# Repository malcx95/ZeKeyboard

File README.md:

# ZeKeyboard

ZeKeyboard is a series of home-made RGB-backlit mechanical keyboards, 
with 3D-printed bodies and custom firmware. 3 keyboards have been made,
one with 60% layout, one with a full size layout, and most recently one
with a 60% layout plus a numpad (the "V2" keyboard). This repository contains all the source
code for the firmware, as well as the 3D-models of the keyboards.

## Layout and body

The first keyboard was the one with the 60% layout, pictured below. It uses the ANSI-style Enter-key,
as well as the ISO-style left-shift key.

The layout for this keyboard was partially generated using scripts and 
template OpenSCAD-files by [TheZoq2](https://github.com/TheZoq2/), which
you can find [here](https://github.com/TheZoq2/Keyboard). These OpenSCAD-files
contained the switch holes corresponding to the json-layout generated from 
[here](http://www.keyboard-layout-editor.com/), and were modeled further
in Blender to form a keyboard body.

The layout for the fullsize keyboard (picture unavailable) and the V2 keyboard (pictured below)
could not be generated using the aforementioned script, so they were manually modeled
in Blender from the json-layout generated from [here](http://www.keyboard-layout-editor.com/).
The V2 body also features carbon fibre handrests.

## Switches

All keyboards use Gateron Brown mechanical switches, which are very similar to 
Cherry MX Brown, in the sense that they have tactile feedback without a click. These
particular switches are the SMD-LED-compatible ones, meaning they have a white body
with clear top, and a large hole for an SMD-LED to shine through.

## Backlight

The backlight consists of Adafruit Neopixel RGB-LEDs. Each LED is hot-glued in place
right below each switch to shine through the 
hole in the switch, lighting up the keycap. This lights
each keycap up more uniformly than LED:s mounted right below the keycap.
On the 60% and V2 keyboard are also two extra LED:s for the spacebar, to the left and right of the main LED.

On the V2 keyboard, there are three LED:s shining inside a cavity in the handrest, illuminating
the ZeKeyboard logo.

## Controller

For the 60% keyboard, the controller used is a Teensy 3.2. I could have chosen a cheaper Teensy, like
Teensy LC, but I wanted enough computing power for the effects I was going to implement.
Also, at the time of purchase, I had a different approach to implementing the 
backlight (involving five TLC5940 chips), which required the extra ports available on the
more expensive Teensy 3.2.

For the other keyboards, due to the larger number of keys, a Teensy 3.5 is used, as it's faster
and has more RAM.

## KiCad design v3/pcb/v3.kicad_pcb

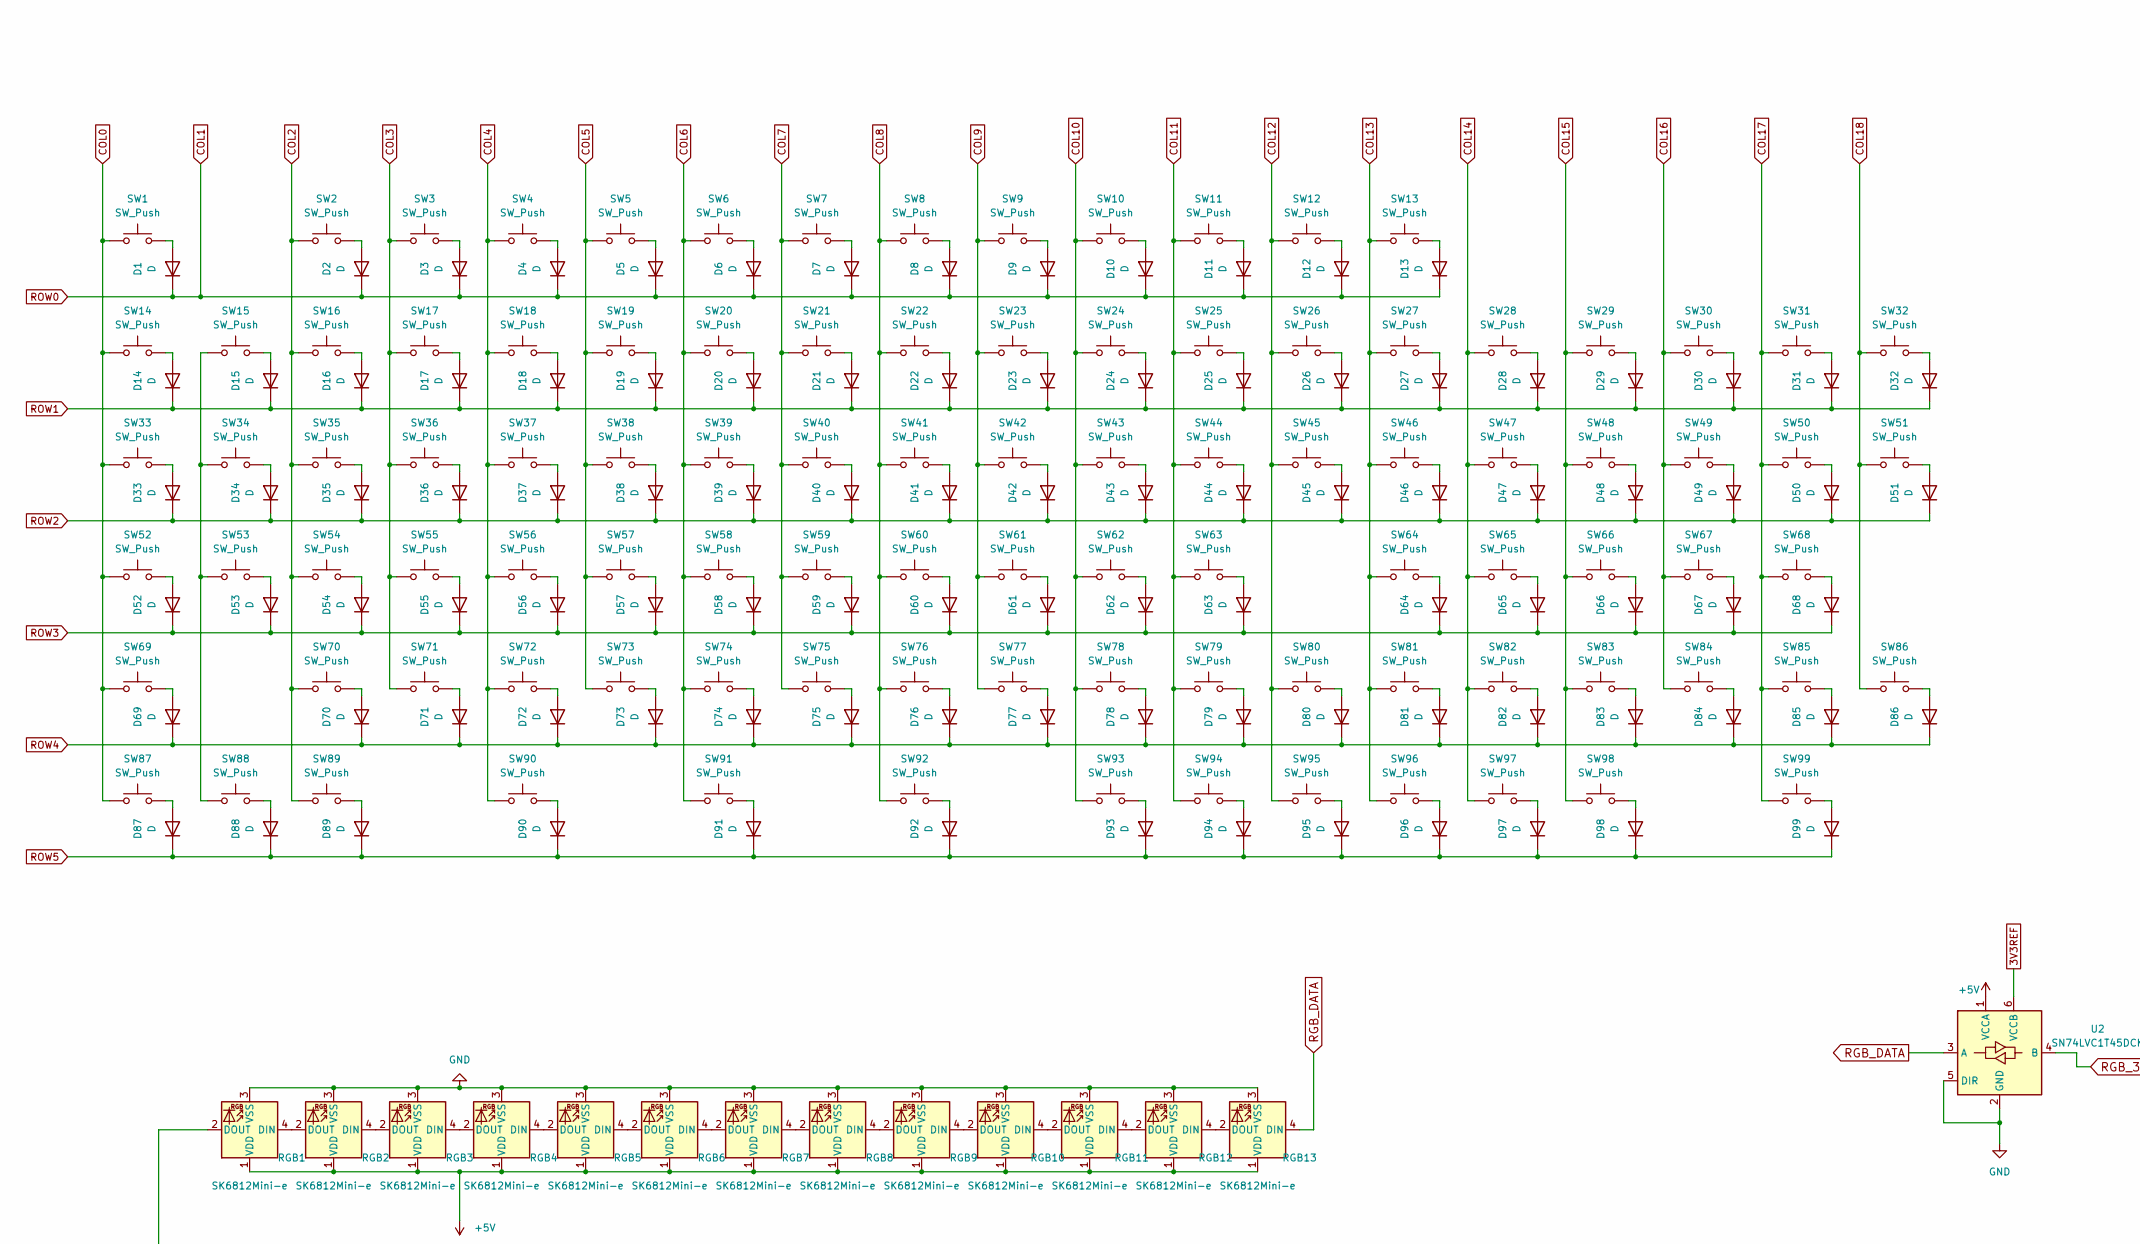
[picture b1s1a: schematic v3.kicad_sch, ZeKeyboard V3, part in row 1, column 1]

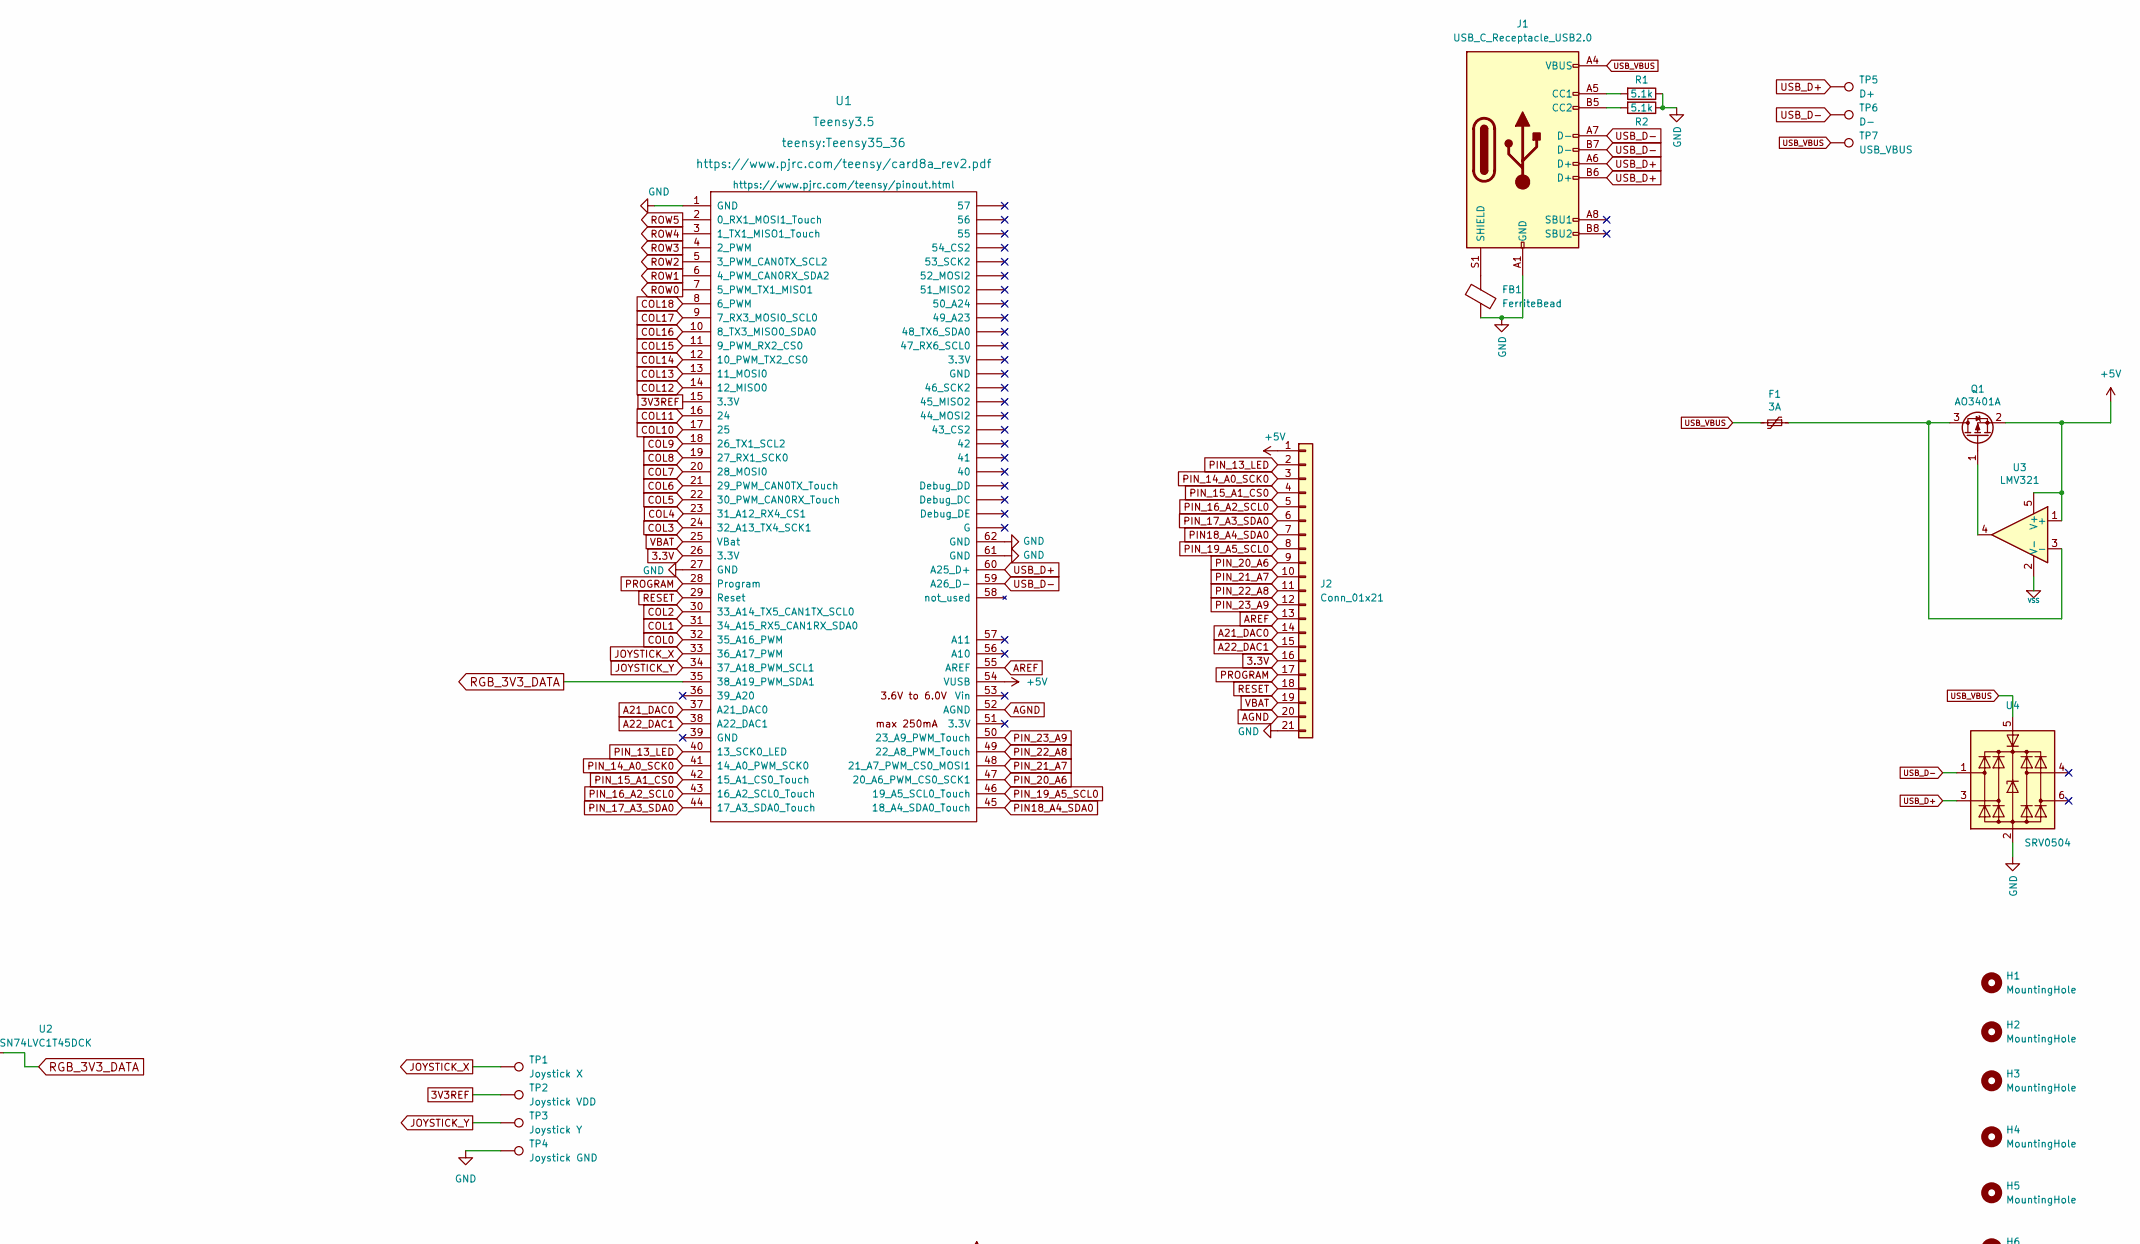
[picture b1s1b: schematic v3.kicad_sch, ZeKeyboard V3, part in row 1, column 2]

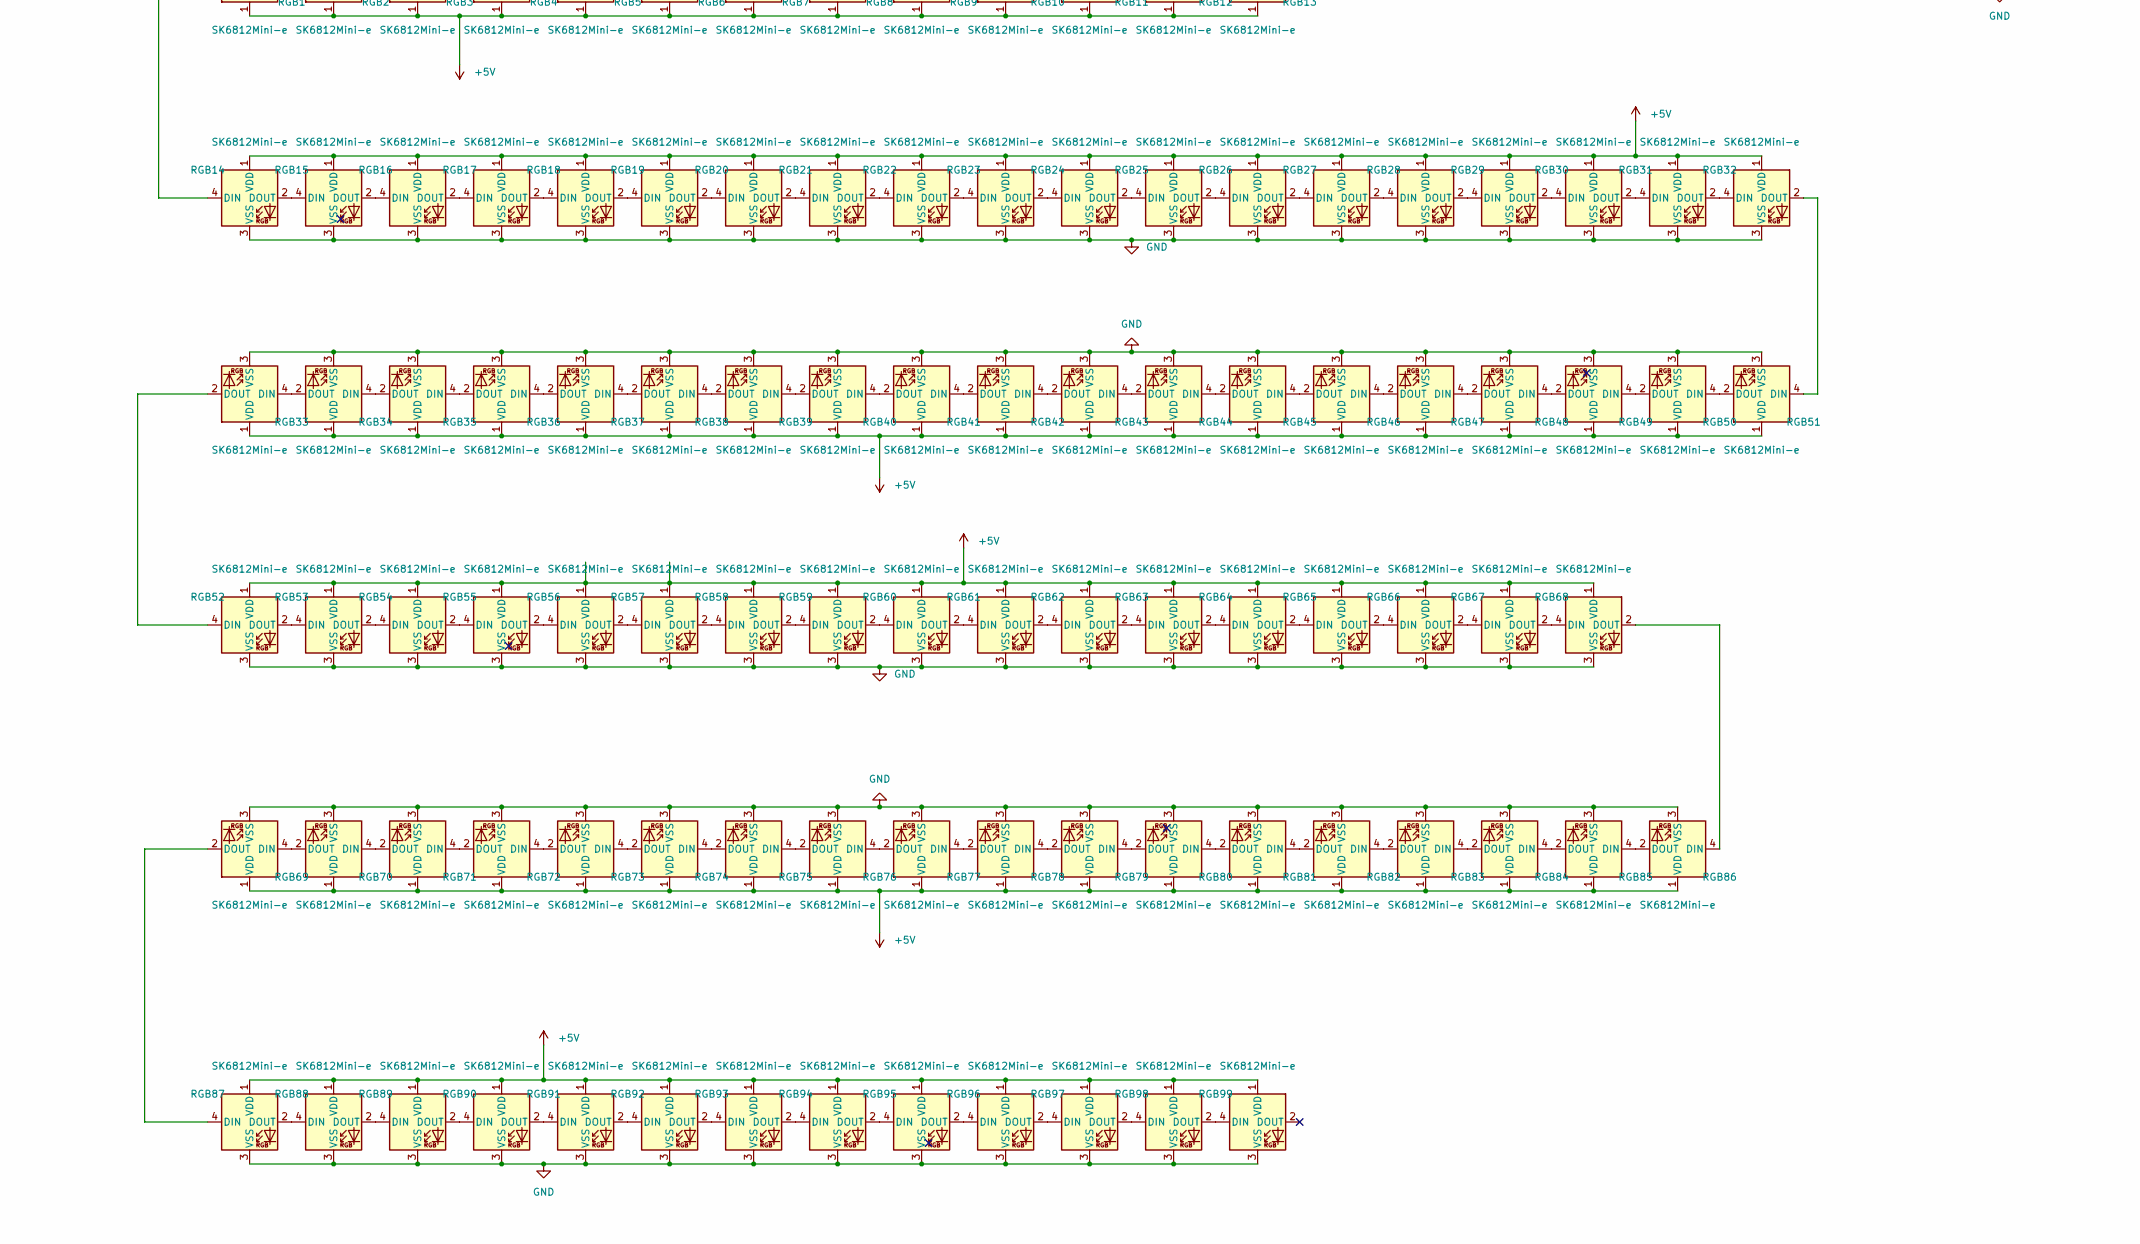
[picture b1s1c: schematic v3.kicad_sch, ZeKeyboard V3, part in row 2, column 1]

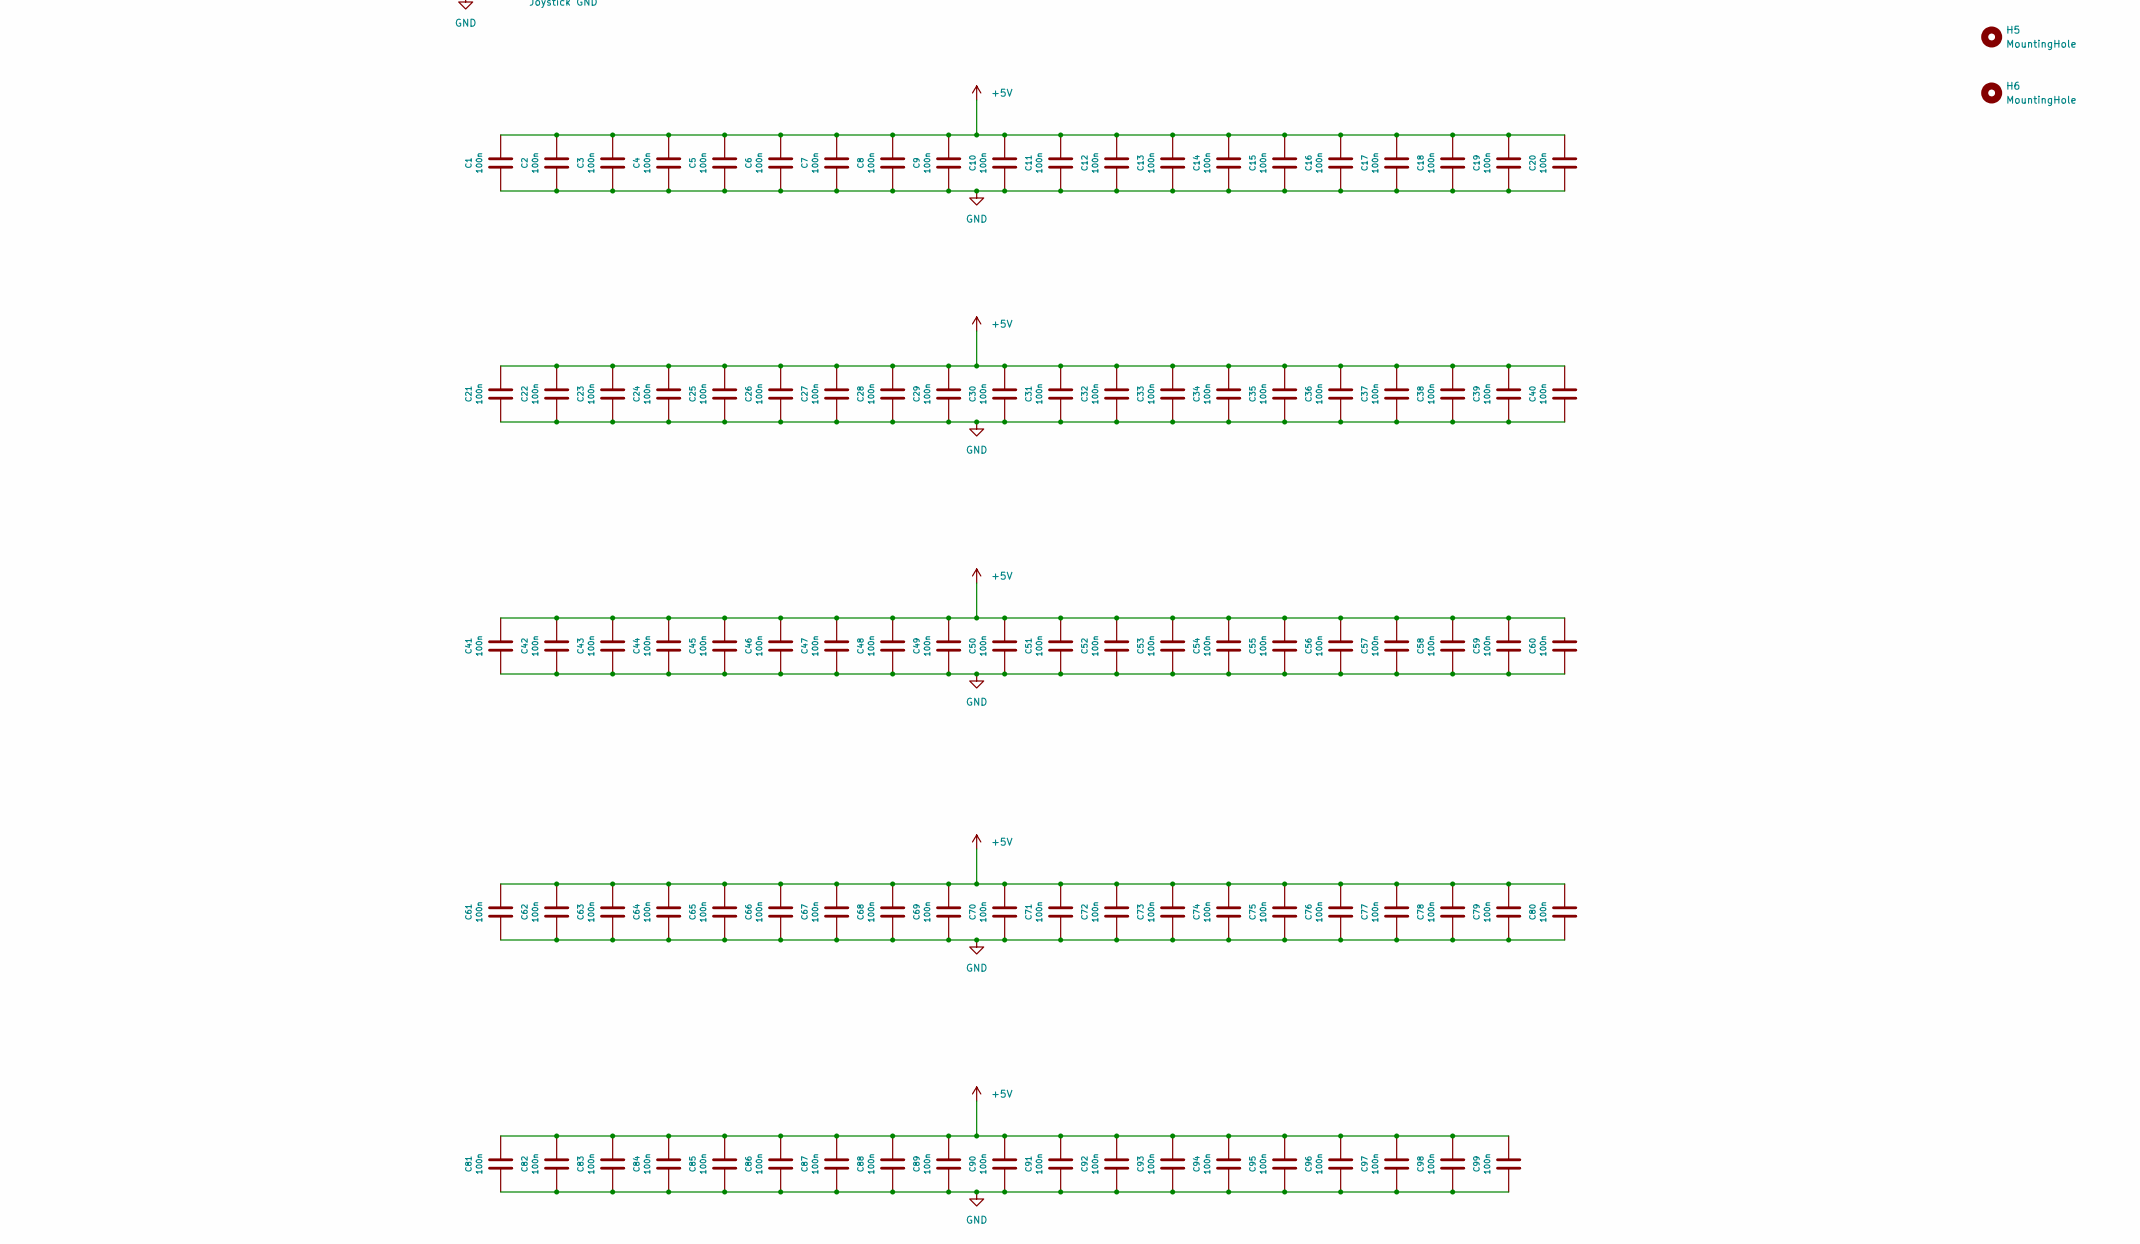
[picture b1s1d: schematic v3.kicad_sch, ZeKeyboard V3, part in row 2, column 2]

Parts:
C1, C2, C3, C4, C5, C6, C7, C8, C9, C10, C11, C12, C13, C14, C15, C16, C17, C18, C19, C20, C21, C22, C23, C24, C25, C26, C27, C28, C29, C30, C31, C32, C33, C34, C35, C36, C37, C38, C39, C40, C41, C42, C43, C44, C45, C46, C47, C48, C49, C50, C51, C52, C53, C54, C55, C56, C57, C58, C59, C60, C61, C62, C63, C64, C65, C66, C67, C68, C69, C70, C71, C72, C73, C74, C75, C76, C77, C78, C79, C80, C81, C82, C83, C84, C85, C86, C87, C88, C89, C90, C91, C92, C93, C94, C95, C96, C97, C98, C99: 100n; SMD-0603; LCSC Part C14663
D1, D2, D3, D4, D5, D6, D7, D8, D9, D10, D11, D12, D13, D14, D15, D16, D17, D18, D19, D20, D21, D22, D23, D24, D25, D26, D27, D28, D29, D30, D31, D32, D33, D34, D35, D36, D37, D38, D39, D40, D41, D42, D43, D44, D45, D46, D47, D48, D49, D50, D51, D52, D53, D54, D55, D56, D57, D58, D59, D60, D61, D62, D63, D64, D65, D66, D67, D68, D69, D70, D71, D72, D73, D74, D75, D76, D77, D78, D79, D80, D81, D82, D83, D84, D85, D86, D87, D88, D89, D90, D91, D92, D93, D94, D95, D96, D97, D98, D99: D; D_SOD-323F
F1: 3A; Fuse_1206_3216Metric; LCSC Part C70085
FB1: FerriteBead; R_0402_1005Metric; LCSC C668229
H1, H2, H3, H4, H5, H6: MountingHole; MountingHole_3.5mm
J1: USB_C_Receptacle_USB2.0; USB_C_Receptacle_HRO_TYPE-C-31-M-12
J2: Conn_01x21; PinHeader_1x21_P2.00mm_Vertical
Q1: AO3401A; SOT-23; LCSC Part C15127
R1, R2: 5.1k; R_0603_1608Metric; Mouser C27834
RGB1, RGB2, RGB3, RGB4, RGB5, RGB6, RGB7, RGB8, RGB9, RGB10, RGB11, RGB12, RGB13, RGB14, RGB15, RGB16, RGB17, RGB18, RGB19, RGB20, RGB21, RGB22, RGB23, RGB24, RGB25, RGB26, RGB27, RGB28, RGB29, RGB30, RGB31, RGB32, RGB33, RGB34, RGB35, RGB36, RGB37, RGB38, RGB39, RGB40, RGB41, RGB42, RGB43, RGB44, RGB45, RGB46, RGB47, RGB48, RGB49, RGB50, RGB51, RGB52, RGB53, RGB54, RGB55, RGB56, RGB57, RGB58, RGB59, RGB60, RGB61, RGB62, RGB63, RGB64, RGB65, RGB66, RGB67, RGB68, RGB69, RGB70, RGB71, RGB72, RGB73, RGB74, RGB75, RGB76, RGB77, RGB78, RGB79, RGB80, RGB81, RGB82, RGB83, RGB84, RGB85, RGB86, RGB87, RGB88, RGB89, RGB90, RGB91, RGB92, RGB93, RGB94, RGB95, RGB96, RGB97, RGB98, RGB99: SK6812Mini-e; SK6812_mini_e_flipable; JLCPCB BOM 0
SW1, SW2, SW3, SW4, SW5, SW6, SW7, SW8, SW9, SW10, SW11, SW12, SW13, SW14, SW15, SW16, SW17, SW18, SW19, SW20, SW21, SW22, SW23, SW24, SW25, SW26, SW28, SW29, SW30, SW31, SW32, SW33, SW34, SW35, SW36, SW37, SW38, SW39, SW40, SW41, SW42, SW43, SW44, SW45, SW46, SW47, SW48, SW49, SW50, SW52, SW53, SW54, SW55, SW56, SW57, SW58, SW59, SW60, SW61, SW62, SW63, SW65, SW66, SW67, SW68, SW69, SW70, SW71, SW72, SW73, SW74, SW75, SW76, SW77, SW78, SW79, SW80, SW81, SW82, SW83, SW84, SW85, SW87, SW88, SW89, SW90, SW93, SW94, SW95, SW96, SW97, SW99: SW_Push; MX_KAILH_SOCKET_1U
SW27, SW64, SW91, SW92, SW98: SW_Push; MX_KAILH_SOCKET_2U_STAB
SW51, SW86: SW_Push; MX_KAILH_SOCKET_2U_STAB_VERT
TP1: Joystick X; TestPoint_THTPad_D1.5mm_Drill0.7mm
TP2: Joystick VDD; TestPoint_THTPad_D1.5mm_Drill0.7mm
TP3: Joystick Y; TestPoint_THTPad_D1.5mm_Drill0.7mm
TP4: Joystick GND; TestPoint_THTPad_D1.5mm_Drill0.7mm
TP5: D+; TestPoint_THTPad_D1.5mm_Drill0.7mm
TP6: D-; TestPoint_THTPad_D1.5mm_Drill0.7mm
TP7: USB_VBUS; TestPoint_THTPad_D1.5mm_Drill0.7mm
U1: Teensy3.5; Teensy35_36
U2: SN74LVC1T45DCK; SOT-363_SC-70-6
U3: LMV321; SOT-23-5; JLCPCB BOM 1
U4: SRV0504; SOT-23-6; JLCPCB BOM 1

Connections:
3.3V: J2.16, U1.26 (3.3V)
3V3REF: TP2.1, U1.15 (3.3V), U2.6 (VCCB)
+5V: C1.1, C2.1, C3.1, C4.1, C5.1, C6.1, C7.1, C8.1, C9.1, C10.1, C11.1, C12.1, C13.1, C14.1, C15.1, C16.1, C17.1, C18.1, C19.1, C20.1, C21.1, C22.1, C23.1, C24.1, C25.1, C26.1, C27.1, C28.1, C29.1, C30.1, C31.1, C32.1, C33.1, C34.1, C35.1, C36.1, C37.1, C38.1, C39.1, C40.1, C41.1, C42.1, C43.1, C44.1, C45.1, C46.1, C47.1, C48.1, C49.1, C50.1, C51.1, C52.1, C53.1, C54.1, C55.1, C56.1, C57.1, C58.1, C59.1, C60.1, C61.1, C62.1, C63.1, C64.1, C65.1, C66.1, C67.1, C68.1, C69.1, C70.1, C71.1, C72.1, C73.1, C74.1, C75.1, C76.1, C77.1, C78.1, C79.1, C80.1, C81.1, C82.1, C83.1, C84.1, C85.1, C86.1, C87.1, C88.1, C89.1, C90.1, C91.1, C92.1, C93.1, C94.1, C95.1, C96.1, C97.1, C98.1, C99.1, J2.1, Q1.2 (S), RGB1.1 (VDD), RGB2.1 (VDD), RGB3.1 (VDD), RGB4.1 (VDD), RGB5.1 (VDD), RGB6.1 (VDD), RGB7.1 (VDD), RGB8.1 (VDD), RGB9.1 (VDD), RGB10.1 (VDD), RGB11.1 (VDD), RGB12.1 (VDD), RGB13.1 (VDD), RGB14.1 (VDD), RGB15.1 (VDD), RGB16.1 (VDD), RGB17.1 (VDD), RGB18.1 (VDD), RGB19.1 (VDD), RGB20.1 (VDD), RGB21.1 (VDD), RGB22.1 (VDD), RGB23.1 (VDD), RGB24.1 (VDD), RGB25.1 (VDD), RGB26.1 (VDD), RGB27.1 (VDD), RGB28.1 (VDD), RGB29.1 (VDD), RGB30.1 (VDD), RGB31.1 (VDD), RGB32.1 (VDD), RGB33.1 (VDD), RGB34.1 (VDD), RGB35.1 (VDD), RGB36.1 (VDD), RGB37.1 (VDD), RGB38.1 (VDD), RGB39.1 (VDD), RGB40.1 (VDD), RGB41.1 (VDD), RGB42.1 (VDD), RGB43.1 (VDD), RGB44.1 (VDD), RGB45.1 (VDD), RGB46.1 (VDD), RGB47.1 (VDD), RGB48.1 (VDD), RGB49.1 (VDD), RGB50.1 (VDD), RGB51.1 (VDD), RGB52.1 (VDD), RGB53.1 (VDD), RGB54.1 (VDD), RGB55.1 (VDD), RGB56.1 (VDD), RGB57.1 (VDD), RGB58.1 (VDD), RGB59.1 (VDD), RGB60.1 (VDD), RGB61.1 (VDD), RGB62.1 (VDD), RGB63.1 (VDD), RGB64.1 (VDD), RGB65.1 (VDD), RGB66.1 (VDD), RGB67.1 (VDD), RGB68.1 (VDD), RGB69.1 (VDD), RGB70.1 (VDD), RGB71.1 (VDD), RGB72.1 (VDD), RGB73.1 (VDD), RGB74.1 (VDD), RGB75.1 (VDD), RGB76.1 (VDD), RGB77.1 (VDD), RGB78.1 (VDD), RGB79.1 (VDD), RGB80.1 (VDD), RGB81.1 (VDD), RGB82.1 (VDD), RGB83.1 (VDD), RGB84.1 (VDD), RGB85.1 (VDD), RGB86.1 (VDD), RGB87.1 (VDD), RGB88.1 (VDD), RGB89.1 (VDD), RGB90.1 (VDD), RGB91.1 (VDD), RGB92.1 (VDD), RGB93.1 (VDD), RGB94.1 (VDD), RGB95.1 (VDD), RGB96.1 (VDD), RGB97.1 (VDD), RGB98.1 (VDD), RGB99.1 (VDD), U1.54 (VUSB), U2.1 (VCCA), U3.1 (+), U3.5 (V+)
A21_DAC0: J2.14, U1.37 (A21_DAC0)
A22_DAC1: J2.15, U1.38 (A22_DAC1)
AGND: J2.20, U1.52 (AGND)
AREF: J2.13, U1.55 (AREF)
COL0: SW1.1, SW14.1, SW33.1, SW52.1, SW69.1, SW87.1, U1.32 (35_A16_PWM)
COL1: D1.1 (K), D2.1 (K), D3.1 (K), D4.1 (K), D5.1 (K), D6.1 (K), D7.1 (K), D8.1 (K), D9.1 (K), D10.1 (K), D11.1 (K), D12.1 (K), D13.1 (K), U1.7 (5_PWM_TX1_MISO1), U1.31 (34_A15_RX5_CAN1RX_SDA0)
COL2: SW2.1, SW16.1, SW35.1, SW54.1, SW70.1, SW89.1, U1.30 (33_A14_TX5_CAN1TX_SCL0)
COL3: SW3.1, SW17.1, SW36.1, SW55.1, SW71.1, U1.24 (32_A13_TX4_SCK1)
COL4: SW4.1, SW18.1, SW37.1, SW56.1, SW72.1, SW90.1, U1.23 (31_A12_RX4_CS1)
COL5: SW5.1, SW19.1, SW38.1, SW57.1, SW73.1, U1.22 (30_PWM_CAN0RX_Touch)
COL6: SW6.1, SW20.1, SW39.1, SW58.1, SW74.1, SW91.1, U1.21 (29_PWM_CAN0TX_Touch)
COL7: SW7.1, SW21.1, SW40.1, SW59.1, SW75.1, U1.20 (28_MOSI0)
COL8: SW8.1, SW22.1, SW41.1, SW60.1, SW76.1, SW92.1, U1.19 (27_RX1_SCK0)
COL9: SW9.1, SW23.1, SW42.1, SW61.1, SW77.1, U1.18 (26_TX1_SCL2)
COL10: SW10.1, SW24.1, SW43.1, SW62.1, SW78.1, SW93.1, U1.17 (25)
COL11: SW11.1, SW25.1, SW44.1, SW63.1, SW79.1, SW94.1, U1.16 (24)
COL12: SW12.1, SW26.1, SW45.1, SW80.1, SW95.1, U1.14 (12_MISO0)
COL13: SW13.1, SW27.1, SW46.1, SW64.1, SW81.1, SW96.1, U1.13 (11_MOSI0)
COL14: SW28.1, SW47.1, SW65.1, SW82.1, SW97.1, U1.12 (10_PWM_TX2_CS0)
COL15: SW29.1, SW48.1, SW66.1, SW83.1, SW98.1, U1.11 (9_PWM_RX2_CS0)
COL16: SW30.1, SW49.1, SW67.1, SW84.1, U1.10 (8_TX3_MISO0_SDA0)
COL17: SW31.1, SW50.1, SW68.1, SW85.1, SW99.1, U1.9 (7_RX3_MOSI0_SCL0)
COL18: SW32.1, SW51.1, SW86.1, U1.8 (6_PWM)
GND: C1.2, C2.2, C3.2, C4.2, C5.2, C6.2, C7.2, C8.2, C9.2, C10.2, C11.2, C12.2, C13.2, C14.2, C15.2, C16.2, C17.2, C18.2, C19.2, C20.2, C21.2, C22.2, C23.2, C24.2, C25.2, C26.2, C27.2, C28.2, C29.2, C30.2, C31.2, C32.2, C33.2, C34.2, C35.2, C36.2, C37.2, C38.2, C39.2, C40.2, C41.2, C42.2, C43.2, C44.2, C45.2, C46.2, C47.2, C48.2, C49.2, C50.2, C51.2, C52.2, C53.2, C54.2, C55.2, C56.2, C57.2, C58.2, C59.2, C60.2, C61.2, C62.2, C63.2, C64.2, C65.2, C66.2, C67.2, C68.2, C69.2, C70.2, C71.2, C72.2, C73.2, C74.2, C75.2, C76.2, C77.2, C78.2, C79.2, C80.2, C81.2, C82.2, C83.2, C84.2, C85.2, C86.2, C87.2, C88.2, C89.2, C90.2, C91.2, C92.2, C93.2, C94.2, C95.2, C96.2, C97.2, C98.2, C99.2, FB1.2, J1.A1 (GND), J1.A12 (GND), J1.B1 (GND), J1.B12 (GND), J2.21, R1.1, R2.1, RGB1.3 (VSS), RGB2.3 (VSS), RGB3.3 (VSS), RGB4.3 (VSS), RGB5.3 (VSS), RGB6.3 (VSS), RGB7.3 (VSS), RGB8.3 (VSS), RGB9.3 (VSS), RGB10.3 (VSS), RGB11.3 (VSS), RGB12.3 (VSS), RGB13.3 (VSS), RGB14.3 (VSS), RGB15.3 (VSS), RGB16.3 (VSS), RGB17.3 (VSS), RGB18.3 (VSS), RGB19.3 (VSS), RGB20.3 (VSS), RGB21.3 (VSS), RGB22.3 (VSS), RGB23.3 (VSS), RGB24.3 (VSS), RGB25.3 (VSS), RGB26.3 (VSS), RGB27.3 (VSS), RGB28.3 (VSS), RGB29.3 (VSS), RGB30.3 (VSS), RGB31.3 (VSS), RGB32.3 (VSS), RGB33.3 (VSS), RGB34.3 (VSS), RGB35.3 (VSS), RGB36.3 (VSS), RGB37.3 (VSS), RGB38.3 (VSS), RGB39.3 (VSS), RGB40.3 (VSS), RGB41.3 (VSS), RGB42.3 (VSS), RGB43.3 (VSS), RGB44.3 (VSS), RGB45.3 (VSS), RGB46.3 (VSS), RGB47.3 (VSS), RGB48.3 (VSS), RGB49.3 (VSS), RGB50.3 (VSS), RGB51.3 (VSS), RGB52.3 (VSS), RGB53.3 (VSS), RGB54.3 (VSS), RGB55.3 (VSS), RGB56.3 (VSS), RGB57.3 (VSS), RGB58.3 (VSS), RGB59.3 (VSS), RGB60.3 (VSS), RGB61.3 (VSS), RGB62.3 (VSS), RGB63.3 (VSS), RGB64.3 (VSS), RGB65.3 (VSS), RGB66.3 (VSS), RGB67.3 (VSS), RGB68.3 (VSS), RGB69.3 (VSS), RGB70.3 (VSS), RGB71.3 (VSS), RGB72.3 (VSS), RGB73.3 (VSS), RGB74.3 (VSS), RGB75.3 (VSS), RGB76.3 (VSS), RGB77.3 (VSS), RGB78.3 (VSS), RGB79.3 (VSS), RGB80.3 (VSS), RGB81.3 (VSS), RGB82.3 (VSS), RGB83.3 (VSS), RGB84.3 (VSS), RGB85.3 (VSS), RGB86.3 (VSS), RGB87.3 (VSS), RGB88.3 (VSS), RGB89.3 (VSS), RGB90.3 (VSS), RGB91.3 (VSS), RGB92.3 (VSS), RGB93.3 (VSS), RGB94.3 (VSS), RGB95.3 (VSS), RGB96.3 (VSS), RGB97.3 (VSS), RGB98.3 (VSS), RGB99.3 (VSS), TP4.1, U1.1 (GND), U1.27 (GND), U1.61 (GND), U1.62 (GND), U2.2 (GND), U2.5 (DIR), U4.2 (GND)
JOYSTICK_X: TP1.1, U1.33 (36_A17_PWM)
JOYSTICK_Y: TP3.1, U1.34 (37_A18_PWM_SCL1)
unnamed: D1.2 (A), SW1.2
unnamed: D2.2 (A), SW2.2
unnamed: D3.2 (A), SW3.2
unnamed: D4.2 (A), SW4.2
unnamed: D5.2 (A), SW5.2
unnamed: D6.2 (A), SW6.2
unnamed: D7.2 (A), SW7.2
unnamed: D8.2 (A), SW8.2
unnamed: D9.2 (A), SW9.2
unnamed: D10.2 (A), SW10.2
unnamed: D11.2 (A), SW11.2
unnamed: D12.2 (A), SW12.2
unnamed: D13.2 (A), SW13.2
unnamed: D14.2 (A), SW14.2
unnamed: D15.2 (A), SW15.2
unnamed: D16.2 (A), SW16.2
unnamed: D17.2 (A), SW17.2
unnamed: D18.2 (A), SW18.2
unnamed: D19.2 (A), SW19.2
unnamed: D20.2 (A), SW20.2
unnamed: D21.2 (A), SW21.2
unnamed: D22.2 (A), SW22.2
unnamed: D23.2 (A), SW23.2
unnamed: D24.2 (A), SW24.2
unnamed: D25.2 (A), SW25.2
unnamed: D26.2 (A), SW26.2
unnamed: D27.2 (A), SW27.2
unnamed: D28.2 (A), SW28.2
unnamed: D29.2 (A), SW29.2
unnamed: D30.2 (A), SW30.2
unnamed: D31.2 (A), SW31.2
unnamed: D32.2 (A), SW32.2
unnamed: D33.2 (A), SW33.2
unnamed: D34.2 (A), SW34.2
unnamed: D35.2 (A), SW35.2
unnamed: D36.2 (A), SW36.2
unnamed: D37.2 (A), SW37.2
unnamed: D38.2 (A), SW38.2
unnamed: D39.2 (A), SW39.2
unnamed: D40.2 (A), SW40.2
unnamed: D41.2 (A), SW41.2
unnamed: D42.2 (A), SW42.2
unnamed: D43.2 (A), SW43.2
unnamed: D44.2 (A), SW44.2
unnamed: D45.2 (A), SW45.2
unnamed: D46.2 (A), SW46.2
unnamed: D47.2 (A), SW47.2
unnamed: D48.2 (A), SW48.2
unnamed: D49.2 (A), SW49.2
unnamed: D50.2 (A), SW50.2
unnamed: D51.2 (A), SW51.2
unnamed: D52.2 (A), SW52.2
unnamed: D53.2 (A), SW53.2
unnamed: D54.2 (A), SW54.2
unnamed: D55.2 (A), SW55.2
unnamed: D56.2 (A), SW56.2
unnamed: D57.2 (A), SW57.2
unnamed: D58.2 (A), SW58.2
unnamed: D59.2 (A), SW59.2
unnamed: D60.2 (A), SW60.2
unnamed: D61.2 (A), SW61.2
unnamed: D62.2 (A), SW62.2
unnamed: D63.2 (A), SW63.2
unnamed: D64.2 (A), SW64.2
unnamed: D65.2 (A), SW65.2
unnamed: D66.2 (A), SW66.2
unnamed: D67.2 (A), SW67.2
unnamed: D68.2 (A), SW68.2
unnamed: D69.2 (A), SW69.2
unnamed: D70.2 (A), SW70.2
unnamed: D71.2 (A), SW71.2
unnamed: D72.2 (A), SW72.2
unnamed: D73.2 (A), SW73.2
unnamed: D74.2 (A), SW74.2
unnamed: D75.2 (A), SW75.2
unnamed: D76.2 (A), SW76.2
unnamed: D77.2 (A), SW77.2
unnamed: D78.2 (A), SW78.2
unnamed: D79.2 (A), SW79.2
unnamed: D80.2 (A), SW80.2
unnamed: D81.2 (A), SW81.2
unnamed: D82.2 (A), SW82.2
unnamed: D83.2 (A), SW83.2
unnamed: D84.2 (A), SW84.2
unnamed: D85.2 (A), SW85.2
unnamed: D86.2 (A), SW86.2
unnamed: D87.2 (A), SW87.2
unnamed: D88.2 (A), SW88.2
unnamed: D89.2 (A), SW89.2
unnamed: D90.2 (A), SW90.2
unnamed: D91.2 (A), SW91.2
unnamed: D92.2 (A), SW92.2
unnamed: D93.2 (A), SW93.2
unnamed: D94.2 (A), SW94.2
unnamed: D95.2 (A), SW95.2
unnamed: D96.2 (A), SW96.2
unnamed: D97.2 (A), SW97.2
unnamed: D98.2 (A), SW98.2
unnamed: D99.2 (A), SW99.2
unnamed: F1.1, Q1.3 (D), U3.3 (-)
unnamed: FB1.1, J1.S1 (SHIELD)
unnamed: J1.A5 (CC1), R1.2
unnamed: J1.B5 (CC2), R2.2
unnamed: Q1.1 (G), U3.4
unnamed: RGB1.2 (DOUT), RGB14.4 (DIN)
unnamed: RGB1.4 (DIN), RGB2.2 (DOUT)
unnamed: RGB2.4 (DIN), RGB3.2 (DOUT)
unnamed: RGB3.4 (DIN), RGB4.2 (DOUT)
unnamed: RGB4.4 (DIN), RGB5.2 (DOUT)
unnamed: RGB5.4 (DIN), RGB6.2 (DOUT)
unnamed: RGB6.4 (DIN), RGB7.2 (DOUT)
unnamed: RGB7.4 (DIN), RGB8.2 (DOUT)
unnamed: RGB8.4 (DIN), RGB9.2 (DOUT)
unnamed: RGB9.4 (DIN), RGB10.2 (DOUT)
unnamed: RGB10.4 (DIN), RGB11.2 (DOUT)
unnamed: RGB11.4 (DIN), RGB12.2 (DOUT)
unnamed: RGB12.4 (DIN), RGB13.2 (DOUT)
unnamed: RGB14.2 (DOUT), RGB15.4 (DIN)
unnamed: RGB15.2 (DOUT), RGB16.4 (DIN)
unnamed: RGB16.2 (DOUT), RGB17.4 (DIN)
unnamed: RGB17.2 (DOUT), RGB18.4 (DIN)
unnamed: RGB18.2 (DOUT), RGB19.4 (DIN)
unnamed: RGB19.2 (DOUT), RGB20.4 (DIN)
unnamed: RGB20.2 (DOUT), RGB21.4 (DIN)
unnamed: RGB21.2 (DOUT), RGB22.4 (DIN)
unnamed: RGB22.2 (DOUT), RGB23.4 (DIN)
unnamed: RGB23.2 (DOUT), RGB24.4 (DIN)
unnamed: RGB24.2 (DOUT), RGB25.4 (DIN)
unnamed: RGB25.2 (DOUT), RGB26.4 (DIN)
unnamed: RGB26.2 (DOUT), RGB27.4 (DIN)
unnamed: RGB27.2 (DOUT), RGB28.4 (DIN)
unnamed: RGB28.2 (DOUT), RGB29.4 (DIN)
unnamed: RGB29.2 (DOUT), RGB30.4 (DIN)
unnamed: RGB30.2 (DOUT), RGB31.4 (DIN)
unnamed: RGB31.2 (DOUT), RGB32.4 (DIN)
unnamed: RGB32.2 (DOUT), RGB51.4 (DIN)
unnamed: RGB33.2 (DOUT), RGB52.4 (DIN)
unnamed: RGB33.4 (DIN), RGB34.2 (DOUT)
unnamed: RGB34.4 (DIN), RGB35.2 (DOUT)
unnamed: RGB35.4 (DIN), RGB36.2 (DOUT)
unnamed: RGB36.4 (DIN), RGB37.2 (DOUT)
unnamed: RGB37.4 (DIN), RGB38.2 (DOUT)
unnamed: RGB38.4 (DIN), RGB39.2 (DOUT)
unnamed: RGB39.4 (DIN), RGB40.2 (DOUT)
unnamed: RGB40.4 (DIN), RGB41.2 (DOUT)
unnamed: RGB41.4 (DIN), RGB42.2 (DOUT)
unnamed: RGB42.4 (DIN), RGB43.2 (DOUT)
unnamed: RGB43.4 (DIN), RGB44.2 (DOUT)
unnamed: RGB44.4 (DIN), RGB45.2 (DOUT)
unnamed: RGB45.4 (DIN), RGB46.2 (DOUT)
unnamed: RGB46.4 (DIN), RGB47.2 (DOUT)
unnamed: RGB47.4 (DIN), RGB48.2 (DOUT)
unnamed: RGB48.4 (DIN), RGB49.2 (DOUT)
unnamed: RGB49.4 (DIN), RGB50.2 (DOUT)
unnamed: RGB50.4 (DIN), RGB51.2 (DOUT)
unnamed: RGB52.2 (DOUT), RGB53.4 (DIN)
unnamed: RGB53.2 (DOUT), RGB54.4 (DIN)
unnamed: RGB54.2 (DOUT), RGB55.4 (DIN)
unnamed: RGB55.2 (DOUT), RGB56.4 (DIN)
unnamed: RGB56.2 (DOUT), RGB57.4 (DIN)
unnamed: RGB57.2 (DOUT), RGB58.4 (DIN)
unnamed: RGB58.2 (DOUT), RGB59.4 (DIN)
unnamed: RGB59.2 (DOUT), RGB60.4 (DIN)
unnamed: RGB60.2 (DOUT), RGB61.4 (DIN)
unnamed: RGB61.2 (DOUT), RGB62.4 (DIN)
unnamed: RGB62.2 (DOUT), RGB63.4 (DIN)
unnamed: RGB63.2 (DOUT), RGB64.4 (DIN)
unnamed: RGB64.2 (DOUT), RGB65.4 (DIN)
unnamed: RGB65.2 (DOUT), RGB66.4 (DIN)
unnamed: RGB66.2 (DOUT), RGB67.4 (DIN)
unnamed: RGB67.2 (DOUT), RGB68.4 (DIN)
unnamed: RGB68.2 (DOUT), RGB86.4 (DIN)
unnamed: RGB69.2 (DOUT), RGB87.4 (DIN)
unnamed: RGB69.4 (DIN), RGB70.2 (DOUT)
unnamed: RGB70.4 (DIN), RGB71.2 (DOUT)
unnamed: RGB71.4 (DIN), RGB72.2 (DOUT)
unnamed: RGB72.4 (DIN), RGB73.2 (DOUT)
unnamed: RGB73.4 (DIN), RGB74.2 (DOUT)
unnamed: RGB74.4 (DIN), RGB75.2 (DOUT)
unnamed: RGB75.4 (DIN), RGB76.2 (DOUT)
unnamed: RGB76.4 (DIN), RGB77.2 (DOUT)
unnamed: RGB77.4 (DIN), RGB78.2 (DOUT)
unnamed: RGB78.4 (DIN), RGB79.2 (DOUT)
unnamed: RGB79.4 (DIN), RGB80.2 (DOUT)
unnamed: RGB80.4 (DIN), RGB81.2 (DOUT)
unnamed: RGB81.4 (DIN), RGB82.2 (DOUT)
unnamed: RGB82.4 (DIN), RGB83.2 (DOUT)
unnamed: RGB83.4 (DIN), RGB84.2 (DOUT)
unnamed: RGB84.4 (DIN), RGB85.2 (DOUT)
unnamed: RGB85.4 (DIN), RGB86.2 (DOUT)
unnamed: RGB87.2 (DOUT), RGB88.4 (DIN)
unnamed: RGB88.2 (DOUT), RGB89.4 (DIN)
unnamed: RGB89.2 (DOUT), RGB90.4 (DIN)
unnamed: RGB90.2 (DOUT), RGB91.4 (DIN)
unnamed: RGB91.2 (DOUT), RGB92.4 (DIN)
unnamed: RGB92.2 (DOUT), RGB93.4 (DIN)
unnamed: RGB93.2 (DOUT), RGB94.4 (DIN)
unnamed: RGB94.2 (DOUT), RGB95.4 (DIN)
unnamed: RGB95.2 (DOUT), RGB96.4 (DIN)
unnamed: RGB96.2 (DOUT), RGB97.4 (DIN)
unnamed: RGB97.2 (DOUT), RGB98.4 (DIN)
unnamed: RGB98.2 (DOUT), RGB99.4 (DIN)
unnamed: SW15.1, SW34.1, SW53.1, SW88.1
PIN18_A4_SDA0: J2.7, U1.45 (18_A4_SDA0_Touch)
PIN_13_LED: J2.2, U1.40 (13_SCK0_LED)
PIN_14_A0_SCK0: J2.3, U1.41 (14_A0_PWM_SCK0)
PIN_15_A1_CS0: J2.4, U1.42 (15_A1_CS0_Touch)
PIN_16_A2_SCL0: J2.5, U1.43 (16_A2_SCL0_Touch)
PIN_17_A3_SDA0: J2.6, U1.44 (17_A3_SDA0_Touch)
PIN_19_A5_SCL0: J2.8, U1.46 (19_A5_SCL0_Touch)
PIN_20_A6: J2.9, U1.47 (20_A6_PWM_CS0_SCK1)
PIN_21_A7: J2.10, U1.48 (21_A7_PWM_CS0_MOSI1)
PIN_22_A8: J2.11, U1.49 (22_A8_PWM_Touch)
PIN_23_A9: J2.12, U1.50 (23_A9_PWM_Touch)
PROGRAM: J2.17, U1.28 (Program)
RESET: J2.18, U1.29 (Reset)
RGB_3V3_DATA: U1.35 (38_A19_PWM_SDA1), U2.4 (B)
RGB_DATA: RGB13.4 (DIN), U2.3 (A)
ROW1: D14.1 (K), D15.1 (K), D16.1 (K), D17.1 (K), D18.1 (K), D19.1 (K), D20.1 (K), D21.1 (K), D22.1 (K), D23.1 (K), D24.1 (K), D25.1 (K), D26.1 (K), D27.1 (K), D28.1 (K), D29.1 (K), D30.1 (K), D31.1 (K), D32.1 (K), U1.6 (4_PWM_CAN0RX_SDA2)
ROW2: D33.1 (K), D34.1 (K), D35.1 (K), D36.1 (K), D37.1 (K), D38.1 (K), D39.1 (K), D40.1 (K), D41.1 (K), D42.1 (K), D43.1 (K), D44.1 (K), D45.1 (K), D46.1 (K), D47.1 (K), D48.1 (K), D49.1 (K), D50.1 (K), D51.1 (K), U1.5 (3_PWM_CAN0TX_SCL2)
ROW3: D52.1 (K), D53.1 (K), D54.1 (K), D55.1 (K), D56.1 (K), D57.1 (K), D58.1 (K), D59.1 (K), D60.1 (K), D61.1 (K), D62.1 (K), D63.1 (K), D64.1 (K), D65.1 (K), D66.1 (K), D67.1 (K), D68.1 (K), U1.4 (2_PWM)
ROW4: D69.1 (K), D70.1 (K), D71.1 (K), D72.1 (K), D73.1 (K), D74.1 (K), D75.1 (K), D76.1 (K), D77.1 (K), D78.1 (K), D79.1 (K), D80.1 (K), D81.1 (K), D82.1 (K), D83.1 (K), D84.1 (K), D85.1 (K), D86.1 (K), U1.3 (1_TX1_MISO1_Touch)
ROW5: D87.1 (K), D88.1 (K), D89.1 (K), D90.1 (K), D91.1 (K), D92.1 (K), D93.1 (K), D94.1 (K), D95.1 (K), D96.1 (K), D97.1 (K), D98.1 (K), D99.1 (K), U1.2 (0_RX1_MOSI1_Touch)
USB_D+: J1.A6 (D+), J1.B6 (D+), TP5.1, U1.60 (A25_D+), U4.3 (I/O2)
USB_D-: J1.A7 (D-), J1.B7 (D-), TP6.1, U1.59 (A26_D-), U4.1 (I/O1)
USB_VBUS: F1.2, J1.A4 (VBUS), J1.A9 (VBUS), J1.B4 (VBUS), J1.B9 (VBUS), TP7.1, U4.5 (VBUS)
VBAT: J2.19, U1.25 (VBat)
VSS: U3.2 (V-)

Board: 2 copper layers, 420 parts (199 on the bottom side), 256 nets, no tracks yet.
